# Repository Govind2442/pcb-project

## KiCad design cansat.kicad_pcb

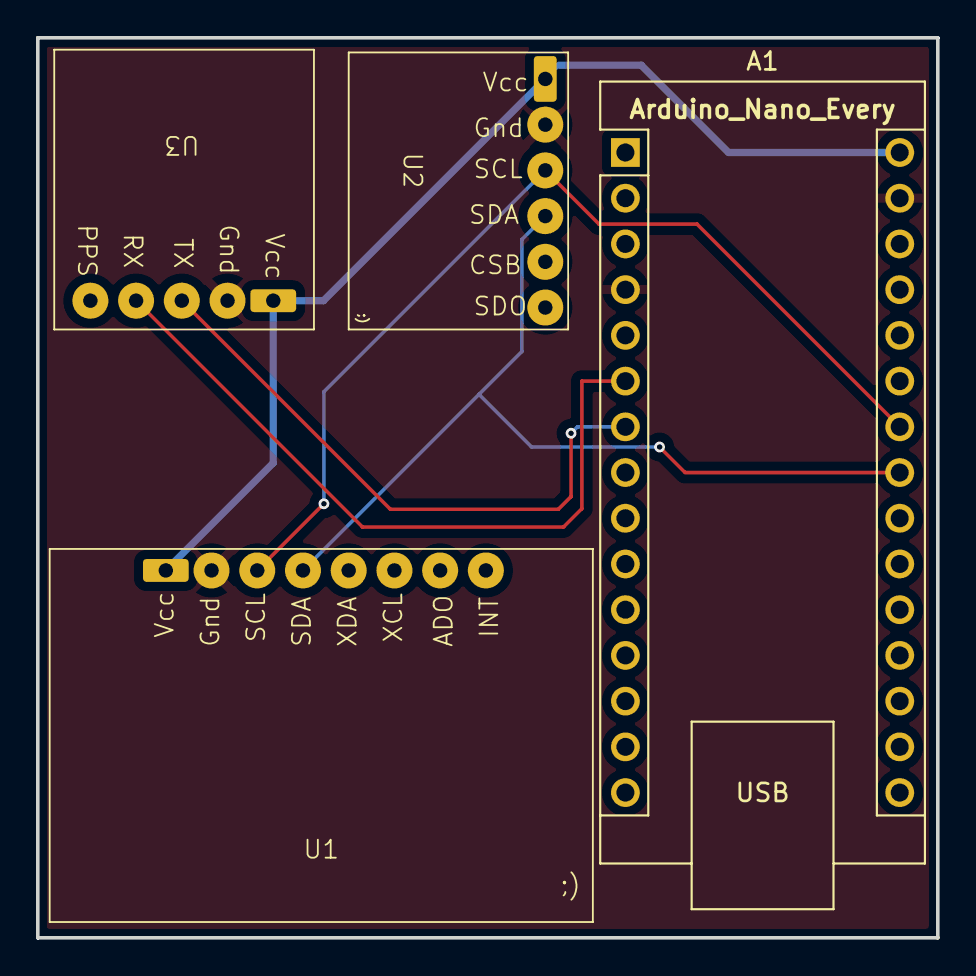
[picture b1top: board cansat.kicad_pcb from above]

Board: 2 copper layers, 50.0 x 50.0 mm, 4 parts (0 on the bottom side), 6 nets.

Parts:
A1: Arduino_Nano_Every; Arduino_Nano
U1: MPU-6050
U2: BMP280
U3: NEO-6m

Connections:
+5V: A1.30 (VIN), U1.1, U2.1 (Vcc), U3.1 (Vcc)
GND: A1.4 (GND), A1.29 (GND), U1.2 (Gnd), U2.2 (Gnd), U3.2 (Gnd)
unnamed: A1.6 (D3), U3.4 (RX)
unnamed: A1.7 (D4), U3.3 (TX)
unnamed: A1.24 (SCL/A5), U1.3 (SCL), U2.3 (SCL)
unnamed: A1.23 (SDA/A4), U1.4 (sda), U2.4 (SDA)

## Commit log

2025-07-20 draft 1
2025-07-23 draft 2 sch chn
2025-07-26 draft 3 pcb chn
2025-08-08 draft 4 sch chn
